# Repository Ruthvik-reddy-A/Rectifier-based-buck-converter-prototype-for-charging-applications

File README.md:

# ⚡ Diode Rectifier Based Buck Converter for Charging Applications

## 🧠 Abstract

With the global push toward electrification, efficient and affordable power converters are essential. This project focuses on designing a **Diode Rectifier Based Buck Converter** capable of:
- Converting 230V AC to <50V DC
- Operating at high efficiency and low ripple
- Remaining compact and cost-effective

Applications include:
- Power supplies
- Battery chargers
- LED lighting
- Electric vehicle components

---

## 🎯 Objectives

- 📉 Step-down voltage with minimal power loss
- ⚡ High-efficiency power conversion
- 📦 Compact design suitable for integration
- 💰 Low-cost hardware (~₹500 total)
- 🔌 Wide AC input voltage tolerance

---

## 🔧 Methodology

### Simulations
- **Software Used**: LTSpice, Simulink
- **Stages**:
  1. **Full-bridge rectifier** simulation with transformer input
  2. **Buck converter** design for voltage and current ripple minimization
  3. **Integrated system analysis** and waveform validation

### Design Specs
- **Transformer**: 230V to 24V, 5A center-tap
- **Calculated duty cycle**: ~46.17%
- **Components**: Inductor, Capacitor, N-Channel MOSFET, Diodes, PWM controller

---

## 📊 Results

### ✅ Simulation Results

- LTSpice and Simulink output waveforms confirm:
  - Stable DC output after rectification
  - Effective voltage regulation with the buck converter
  - Acceptable ripple within target range

### 🧪 Hardware Output

- Constructed and tested physical circuit
- Measured transformer voltage regulation: **~13%**
- Demonstrated consistent output under varying loads
- Also designed a PCB for the product

---

## 💬 Conclusion

The project successfully demonstrates a **low-cost**, **efficient**, and **scalable** full-bridge diode rectifier-based buck converter. This converter can:
- Operate under wide AC input
- Deliver regulated DC output with low ripple
- Serve as a viable solution for fast-charging and regulated DC applications

---

## 🌍 Applications

- AC to DC adapters
- LED lighting systems
- Motor drives
- Electric vehicle subsystems
- Renewable energy interfaces (solar/wind)
- General-purpose low-voltage DC power supplies

---

## 📚 References

- [Elprocus - 230V AC to 5V DC Conversion](https://www.elprocus.com/steps-to-convert-the-230v-ac-to-5v-dc/)
- [Electrical Technology - Buck Converter](https://www.electricaltechnology.org/2020/09/buck-converter.html)
- “Power Electronics: Converters, Application and Design” by Ned Mohan, William Robbins
- “Fundamentals of Power Electronics” by Erickson & Maksimovic
- “Power Electronics” by Muhammad H. Rashid

---

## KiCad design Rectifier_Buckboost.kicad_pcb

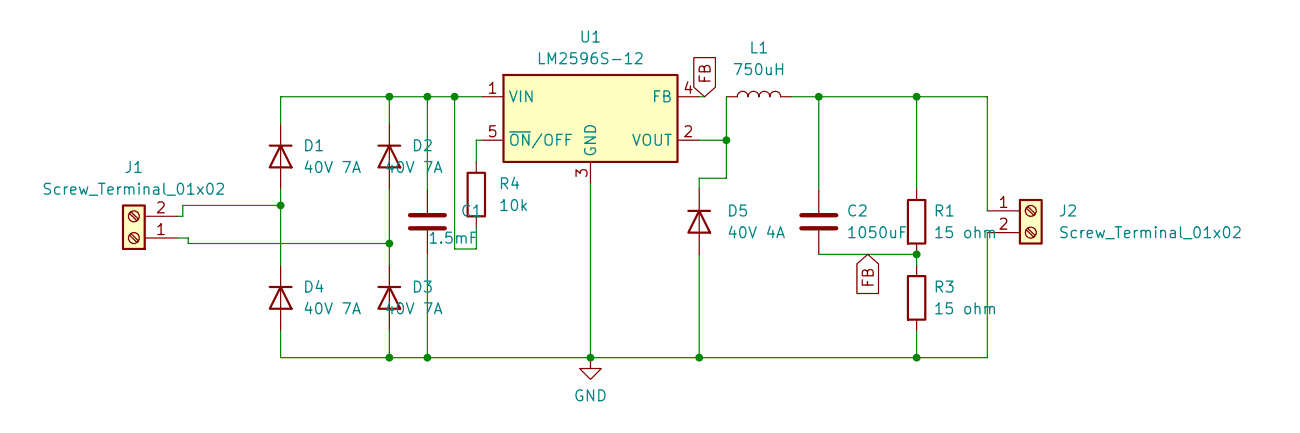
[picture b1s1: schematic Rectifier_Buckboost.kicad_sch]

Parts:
C1: 1.5mF; C_Radial_D12.5mm_H20.0mm_P5.00mm
C2: 1050uF; C_Radial_D10.0mm_H12.5mm_P5.00mm
D1, D2, D3, D4: 40V 7A; D_A-405_P7.62mm_Horizontal
D5: 40V 4A; D_A-405_P7.62mm_Horizontal
J1, J2: Screw_Terminal_01x02; TerminalBlock_Phoenix_MKDS-1,5-2_1x02_P5.00mm_Horizontal
L1: 750uH; L_0201_0603Metric
R1, R3: 15 ohm; R_0201_0603Metric
R4: 10k; R_0201_0603Metric
U1: LM2596S-12; TO-263-5_TabPin3

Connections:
FB: C2.2, R1.2, R3.1, U1.4 (FB)
GND: C1.2, D3.2 (A), D4.2 (A), D5.2 (A), J2.2, R3.2, U1.3 (GND)
unnamed: D1.2 (A), D4.1 (K), J1.2
unnamed: C1.1, D1.1 (K), D2.1 (K), R4.2, U1.1 (VIN)
unnamed: D2.2 (A), D3.1 (K), J1.1
unnamed: D5.1 (K), L1.1, U1.2 (VOUT)
unnamed: C2.1, J2.1, L1.2, R1.1
unnamed: R4.1, U1.5 (~ON/OFF)

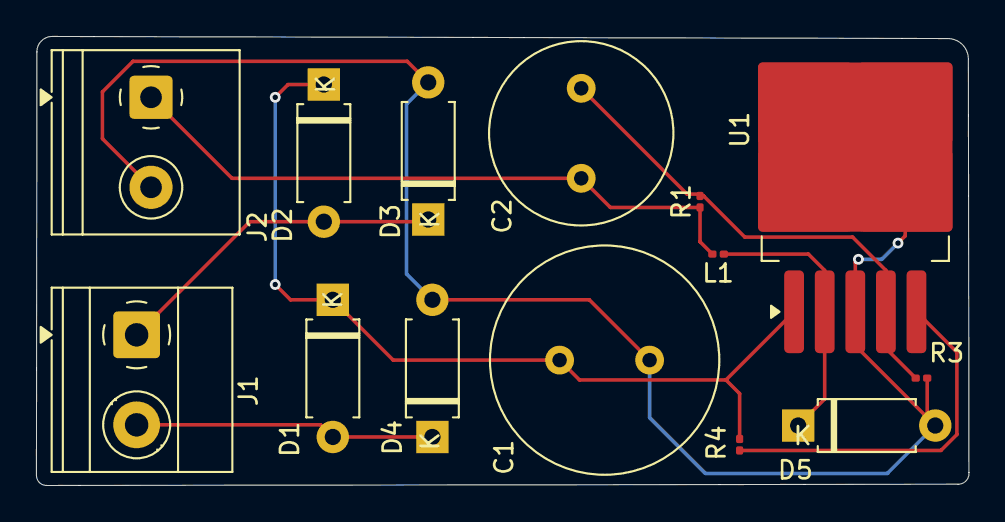
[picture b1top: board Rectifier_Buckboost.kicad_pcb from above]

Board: 2 copper layers, 51.8 x 24.9 mm, 14 parts (0 on the bottom side), 8 nets.

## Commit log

2024-05-16 Update README.md
    In the present-day scenario, we use a lot of chargers and electrical storage devices, as the world is moving more towards electrical side, we need highly efficient power converters and storage devices
    The importance of using diode rectifier buck converter is: High Efficiency
    Compact Size
    Low Cost
    Wide Input Voltage
    Diode rectifier based buck converter is a type of DC-DC converter that uses a diode rectifier and a buck converter to efficiently step down a higher input voltage to a lower outpu
2024-05-16 Rename image.png to Rectifier Buck Converter.png
2024-05-16 Rename Rectifier Buck Converter.png to Rectifier Buck Converter.jpg
2024-05-16 Add files via upload
    5 amps center tapped step down transformer.
2024-05-16 Rename image.png to 5 amps center tapped step down transformer.jpg
2025-06-16 Add KiCad PCB design files for buck converter
